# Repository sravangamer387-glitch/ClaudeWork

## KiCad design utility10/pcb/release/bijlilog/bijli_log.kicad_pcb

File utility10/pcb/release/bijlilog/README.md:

# Bijli Log (power-cut logger) - main board (rev B)

Power-cut logger: USB-C 5 V, 3.3 V LDO, 2 x AAA backup (Schottky OR), OLED, RTC module, mains-present sense.

**Status: engineering release, software-verified only (ERC on the netlist, KiCad DRC, netlist cross-check, SPICE where noted). Not yet built, not reviewed by a second engineer, not certified.**

## Specification
- Board 68 x 52 mm, 2 layers, 1.6 mm FR-4, 1 oz copper, rounded corners R2.5 mm, 4 x M2.5 mounting holes, 2 fiducials.
- Rules used: min track 0.2 mm (power 0.4 mm), min clearance 0.2 mm, via 0.6/0.3 mm, GND pour on both layers, 78 stitching vias.
- Finish: ENIG recommended (HASL lead-free acceptable); green mask, white silk; IPC class 2.
- 31 parts, 19 nets.

## Circuit description
- VBUS -> PTC -> +5V -> AP2112K-3.3 -> +3V3 -> Schottky -> VSYS; battery -> Schottky -> VSYS. Drop about 0.3 V; at 4 MHz the MCU runs down to 1.8 V.
- MAINS = VBUS divided by 100 k/100 k: high while the adapter is powered, low in a cut; the firmware stamps the start (RTC) and measures the duration (pc_* engine).

## Power
Run about 3 mA incl. OLED off most of the time; on battery only during cuts.

## Verification
| Check | Result |
|---|---|
| Electrical rule check on the netlist (own ERC: unconnected pins, single-pin nets, output conflicts, unpowered supplies, symbol/footprint pin match) | 0 errors, 0 warnings |
| KiCad DRC | 0 errors, 0 warnings; unconnected pads: 0 |
| Schematic netlist equals PCB netlist | yes |
| Router failures | 0 |
| 3D STEP export | yes |
| Independent Gerber parse (gerbonara): layers parsed, outline size equals the design | 9 layers, outline [68.1, 52.1] mm, match |

Enclosure (prototype shell for 3D printing): outer 83.2 x 67.2 x 34.8 mm, collision/opening check: pass

## Bill of materials
| Ref | Value | Footprint | Manufacturer part | LCSC # | LCSC status |
|---|---|---|---|---|---|
| U1 | ATmega328P-AU | TQFP-32_7x7mm_P0.8mm | ATMEGA328P-AU | C14877 | verified |
| C1 | 100n | C_0603_1608Metric | Samsung CL10B104KB8NNNC 0603 100nF X7R 50V | C1591 | verified |
| C2 | 100n | C_0603_1608Metric | Samsung CL10B104KB8NNNC 0603 100nF X7R 50V | C1591 | verified |
| C3 | 100n | C_0603_1608Metric | Samsung CL10B104KB8NNNC 0603 100nF X7R 50V | C1591 | verified |
| R7 | 10k | R_0603_1608Metric | 0603 10k 1% | C25804 | verified |
| J2 | ISP | PinHeader_2x03_P2.54mm_Vertical | HCTL PZ254-2-03-Z-8.5 (ZHOURI C5116479 had only 340 in stock) | C2894964 | verified |
| J1 | USB-C 5V | USB_C_Receptacle_HRO_TYPE-C-31-M-12 | TYPE-C-31-M-12 | C165948 | verified |
| F1 | PTC 500mA | Fuse_1206_3216Metric | Littelfuse 1206L050YR (6 V) | C163512 | verified |
| D3 | SMAJ5.0A | D_SMA | Littelfuse SMAJ5.0A | C83329 | verified |
| R1 | 5.1k | R_0603_1608Metric | 0603 5.1k 1% | C23186 | verified |
| R2 | 5.1k | R_0603_1608Metric | 0603 5.1k 1% | C23186 | verified |
| C5 | 10u | C_0805_2012Metric | 0805 10uF X5R | C15850 | verified |
| D1 | Green | LED_0603_1608Metric | Hubei KENTO KT-0603YG yellow-green 570 nm, Vf about 2 V (lights well from 3.3 V with 1 k; the Everlight 19-217 green was out of stock) | C2289 | verified |
| R5 | 1k | R_0603_1608Metric | 0603 1k 1% | C21190 | verified |
| U3 | AP2112K-3.3 | SOT-23-5 | Diodes AP2112K-3.3TRG1 (from the LCSC datasheet link) | C51118 | verified |
| C6 | 1u | C_0603_1608Metric | 0603 1uF X7R | C15849 | verified |
| C7 | 1u | C_0603_1608Metric | 0603 1uF X7R | C15849 | verified |
| D5 | BAT54WS | D_SOD-323 | BORN BAT54WS (300 mA listing) | C5148476 | verified |
| D6 | BAT54WS | D_SOD-323 | BORN BAT54WS (300 mA listing) | C5148476 | verified |
| J6 | BATT 2xAAA backup | JST_PH_B2B-PH-K_1x02_P2.00mm_Vertical | JST B2B-PH-K-S(LF)(SN) | C131337 | verified |
| C8 | 10u | C_0805_2012Metric | 0805 10uF X5R | C15850 | verified |
| R12 | 100k | R_0603_1608Metric | 0603 100k 1% | C25803 | verified |
| R13 | 100k | R_0603_1608Metric | 0603 100k 1% | C25803 | verified |
| J4 | OLED 0.91in I2C | JST_PH_B4B-PH-K_1x04_P2.00mm_Vertical | JST B4B-PH-K-S(LF)(SN) | C131334 | verified |
| J5 | RTC DS3231 module | JST_PH_B4B-PH-K_1x04_P2.00mm_Vertical | JST B4B-PH-K-S(LF)(SN) | C131334 | verified |
| R10 | 4.7k | R_0603_1608Metric | 0603 4.7k 1% | C23162 | verified |
| R11 | 4.7k | R_0603_1608Metric | 0603 4.7k 1% | C23162 | verified |
| SW2 | Scroll / clear | SW_SPST_B3U-1000P | Omron B3U-1000P | C231329 | verified |
| TP1 | TP | TestPoint_Pad_D1.5mm |  |  |  |
| TP2 | TP | TestPoint_Pad_D1.5mm |  |  |  |
| TP3 | TP | TestPoint_Pad_D1.5mm |  |  |  |

`verified` = LCSC number confirmed by web search on 2026-10-31/11-01; `memory` = from my recollection, **check on lcsc.com before ordering**; empty = no number chosen (through-hole connectors, switches, buzzer, test points: hand-assembled or chosen by the buyer). `*_JLC_BOM.csv` / `*_JLC_CPL.csv` list only the parts with an LCSC number; JLCPCB rotation corrections (CPL) must be checked in their viewer.

## Assembly notes
- Reflow (JLCPCB SMT): all SMD parts with an LCSC number. Hand-solder: JST connectors, pin headers, buzzer, switches, test points as listed in the BOM. Fiducials and mounting holes are in the Gerbers.
- Polarity: LED cathode toward GND (silk marks), electrolytic none, diode D2 cathode to +V, Q2 orientation as footprint (SOT-23 pin 1 = gate).
- Programming: ISP header J2 (pin 1 = MISO, square pad). Flash the matching image from `utility10/firmware/release/`: Seeti Counter `4MHz/seeti_prod.hex` (production firmware: timer-triggered 16 kS/s ADC, scan mode to find the real whistle frequency, battery check), Rain Alert `8MHz/rain_alert.hex`, Bijli Meter Reader `8MHz/bijli_meter.hex` (demo-grade firmware, to be hardened).

## Bring-up and test
1. Plug USB: +3V3 = 3.3 V, VSYS about 3.0 V, MAINS (TP3) about 2.5 V.
2. Unplug: MAINS goes low, unit stays alive on the battery, cut logged; replug: duration shown.

## Files
`1_fabrication/` Gerber + drill zip (upload to JLCPCB/any fab), fab notes, copper plot
`2_assembly/` JLC BOM + CPL (SMD parts JLC assembles), full BOM with LCSC numbers for every part, pick-and-place, assembly drawing
`3_design/` KiCad 7 project (pcb, schematic, libs), netlist, STEP model, schematic PDF, renders
`4_enclosure/` printable enclosure (base, screwed lid, battery door, plungers / light pipes / switch extensions) or a mounting plate for a bought IP65 box; dimensions and notes in enclosure.json
`5_verification/` DRC, ERC, verification and readiness reports

## Known limits and review checklist
- Layout was produced by a custom router and software placement; a human layout review (analog routing, ground returns, creepage, connector mechanics, silkscreen) is still required.
- Not verified: EMC, ESD (apart from TVS parts where fitted), thermal, real component tolerances, supplier stock/price, assembly house design-for-manufacture check (run JLCPCB's DFM check on the Gerbers).
- Firmware thresholds are placeholders to be calibrated on prototypes.

## Manufacturing readiness (automatic check)

| Check | Result |
|---|---|
| gerber layers and drill present | PASS |
| drc errors 0 | PASS |
| unconnected 0 | PASS |
| netlist matches schematic | PASS |
| erc errors 0 | PASS |
| independent gerber check clean | PASS |
| every part has lcsc number | PASS |
| every lcsc number verified | PASS |
| cpl rows equal jlc bom parts | PASS |
| step model | PASS |
| KiCad DRC warnings | 0 |
| **Order ready** | **YES** |

Order steps: (1) upload `1_fabrication/*_gerbers.zip`; (2) for assembly upload `2_assembly/*_JLC_BOM.csv` and `*_JLC_CPL.csv`, check the 3D/rotation preview for every polarised part (diodes, ICs, LEDs, electrolytics) because CPL rotations are generated, not hand-checked; (3) buy the through-hole parts listed in `*_BOM_full.csv` marked hand/THT and solder them; (4) re-check stock and the exact LCSC listing for every line before paying.

Limits: the layout is software-generated and has not been reviewed by a PCB engineer; no prototype has been built; the first batch should be treated as a prototype run (order 5 boards).

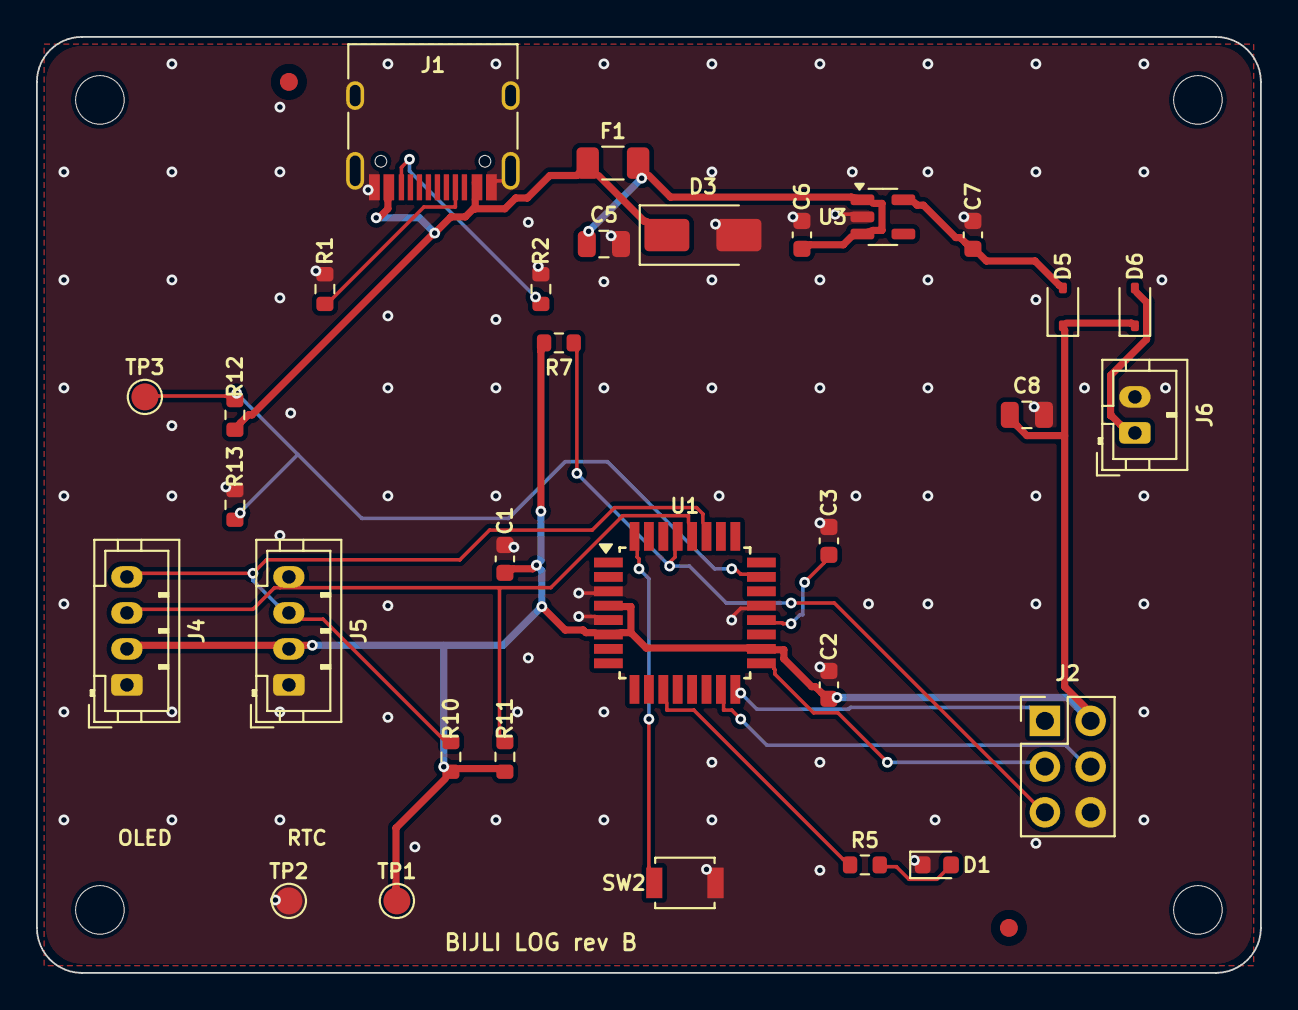
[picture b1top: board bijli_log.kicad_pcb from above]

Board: 2 copper layers, 68.0 x 52.0 mm, 37 parts (0 on the bottom side), 19 nets.

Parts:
C1, C2, C3: 100n; C_0603_1608Metric
C5, C8: 10u; C_0805_2012Metric
C6, C7: 1u; C_0603_1608Metric
D1: Green; LED_0603_1608Metric
D3: SMAJ5.0A; D_SMA
D5, D6: BAT54WS; D_SOD-323
F1: PTC 500mA; Fuse_1206_3216Metric
FID1, FID2: Fiducial; Fiducial_1mm_Mask2mm
H1, H2, H3, H4: M2.5; MountingHole_2.7mm_M2.5
J1: USB-C 5V; USB_C_Receptacle_HRO_TYPE-C-31-M-12
J2: ISP; PinHeader_2x03_P2.54mm_Vertical
J4: OLED 0.91in I2C; JST_PH_B4B-PH-K_1x04_P2.00mm_Vertical
J5: RTC DS3231 module; JST_PH_B4B-PH-K_1x04_P2.00mm_Vertical
J6: BATT 2xAAA backup; JST_PH_B2B-PH-K_1x02_P2.00mm_Vertical
R1, R2: 5.1k; R_0603_1608Metric
R5: 1k; R_0603_1608Metric
R7: 10k; R_0603_1608Metric
R10, R11: 4.7k; R_0603_1608Metric
R12, R13: 100k; R_0603_1608Metric
SW2: Scroll / clear; SW_SPST_B3U-1000P
TP1, TP2, TP3: TP; TestPoint_Pad_D1.5mm
U1: ATmega328P-AU; TQFP-32_7x7mm_P0.8mm
U3: AP2112K-3.3; SOT-23-5

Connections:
+3V3: C7.1, D5.2, U3.5
+5V: C5.1, C6.1, F1.2, U3.1, U3.3
AREF: C3.1, U1.20
BAT_P: D6.2, J6.1
BTN: SW2.1, U1.32
CC1: J1.A5, R1.1
CC2: J1.B5, R2.1
D1_A: D1.2, R5.2
GND: C1.2, C2.2, C3.2, C5.2, C6.2, C7.2, C8.2, D1.1, D3.2, J1.A1, J1.A12, J1.B1, J1.B12, J1.S1, J2.6, J4.1, J5.1, J6.2, R1.2, R2.2, R13.2, SW2.2, TP2.1, U1.3, U1.5, U1.21, U3.2
LED: R5.1, U1.11
MAINS: R12.2, R13.1, TP3.1, U1.23
MISO: J2.1, U1.16
MOSI: J2.4, U1.15
RESET: J2.5, R7.2, U1.29
SCK: J2.3, U1.17
SCL: J4.3, J5.4, R11.2, U1.28
SDA: J4.4, J5.3, R10.2, U1.27
VBUS: D3.1, F1.1, J1.A4, J1.A9, J1.B4, J1.B9, R12.1
VSYS: C1.1, C2.1, C8.1, D5.1, D6.1, J2.2, J4.2, J5.2, R7.1, R10.1, R11.1, TP1.1, U1.4, U1.6, U1.18

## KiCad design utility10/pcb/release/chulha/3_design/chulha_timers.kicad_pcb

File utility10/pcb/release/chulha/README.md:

# Chulha Timers - main board (rev B)

Four independent kitchen timers: four channel buttons, TM1637 6-digit display module, loud buzzer, 3 x AAA.

**Status: engineering release, software-verified only (ERC on the netlist, KiCad DRC, netlist cross-check, SPICE where noted). Not yet built, not reviewed by a second engineer, not certified.**

## Specification
- Board 72 x 48 mm, 2 layers, 1.6 mm FR-4, 1 oz copper, rounded corners R2.5 mm, 4 x M2.5 mounting holes, 2 fiducials.
- Rules used: min track 0.2 mm (power 0.4 mm), min clearance 0.2 mm, via 0.6/0.3 mm, GND pour on both layers, 86 stitching vias.
- Finish: ENIG recommended (HASL lead-free acceptable); green mask, white silk; IPC class 2.
- 22 parts, 18 nets.

## Circuit description
- Channel buttons CH1-CH4 on PD2-PD5 (internal pull-ups); TM1637 on PC4/PC5 (DIO/CLK) through the J4 module header; buzzer driver as on the other boards.
- Tap adds one minute, hold 1 s clears; each channel rings separately (firmware engine ct_*, tested).

## Power
Display on: about 10 mA + MCU 3 mA; sleep between button presses and blank the display after 20 s idle -> months on 3 x AAA.

## Verification
| Check | Result |
|---|---|
| Electrical rule check on the netlist (own ERC: unconnected pins, single-pin nets, output conflicts, unpowered supplies, symbol/footprint pin match) | 0 errors, 0 warnings |
| KiCad DRC | 0 errors, 0 warnings; unconnected pads: 0 |
| Schematic netlist equals PCB netlist | yes |
| Router failures | 0 |
| 3D STEP export | yes |
| Independent Gerber parse (gerbonara): layers parsed, outline size equals the design | 9 layers, outline [72.1, 48.1] mm, match |

Enclosure (prototype shell for 3D printing): outer 87.2 x 63.5 x 35.8 mm, collision/opening check: pass

## Bill of materials
| Ref | Value | Footprint | Manufacturer part | LCSC # | LCSC status |
|---|---|---|---|---|---|
| U1 | ATmega328P-AU | TQFP-32_7x7mm_P0.8mm | ATMEGA328P-AU | C14877 | verified |
| C1 | 100n | C_0603_1608Metric | Samsung CL10B104KB8NNNC 0603 100nF X7R 50V | C1591 | verified |
| C2 | 100n | C_0603_1608Metric | Samsung CL10B104KB8NNNC 0603 100nF X7R 50V | C1591 | verified |
| C3 | 100n | C_0603_1608Metric | Samsung CL10B104KB8NNNC 0603 100nF X7R 50V | C1591 | verified |
| R7 | 10k | R_0603_1608Metric | 0603 10k 1% | C25804 | verified |
| J2 | ISP | PinHeader_2x03_P2.54mm_Vertical | HCTL PZ254-2-03-Z-8.5 (ZHOURI C5116479 had only 340 in stock) | C2894964 | verified |
| J1 | BATT 3xAAA | JST_PH_B2B-PH-K_1x02_P2.00mm_Vertical | JST B2B-PH-K-S(LF)(SN) | C131337 | verified |
| SW1 | Power | SW_SPDT_PCM12 | C&K PCM12SMTR | C221841 | verified |
| Q2 | AO3401A | SOT-23 | AO3401A | C15127 | verified |
| C4 | 10u | C_0805_2012Metric | 0805 10uF X5R | C15850 | verified |
| BZ1 | Buzzer | Buzzer_12x9.5RM7.6 | YUEXIN KC1206 16 ohm passive magnetic 12x9.5 mm (2048 Hz) | C781869 | verified |
| Q1 | MMBT3904 | SOT-23 | MMBT3904 | C20526 | verified |
| D2 | 1N4148WS | D_SOD-323 | 1N4148WS | C2128 | verified |
| R6 | 1k | R_0603_1608Metric | 0603 1k 1% | C21190 | verified |
| SW2 | CH1 | SW_SPST_B3U-1000P | Omron B3U-1000P | C231329 | verified |
| SW3 | CH2 | SW_SPST_B3U-1000P | Omron B3U-1000P | C231329 | verified |
| SW4 | CH3 | SW_SPST_B3U-1000P | Omron B3U-1000P | C231329 | verified |
| SW5 | CH4 | SW_SPST_B3U-1000P | Omron B3U-1000P | C231329 | verified |
| J4 | TM1637 display | JST_PH_B4B-PH-K_1x04_P2.00mm_Vertical | JST B4B-PH-K-S(LF)(SN) | C131334 | verified |
| TP1 | TP | TestPoint_Pad_D1.5mm |  |  |  |
| TP2 | TP | TestPoint_Pad_D1.5mm |  |  |  |
| TP3 | TP | TestPoint_Pad_D1.5mm |  |  |  |

`verified` = LCSC number confirmed by web search on 2026-10-31/11-01; `memory` = from my recollection, **check on lcsc.com before ordering**; empty = no number chosen (through-hole connectors, switches, buzzer, test points: hand-assembled or chosen by the buyer). `*_JLC_BOM.csv` / `*_JLC_CPL.csv` list only the parts with an LCSC number; JLCPCB rotation corrections (CPL) must be checked in their viewer.

## Assembly notes
- Reflow (JLCPCB SMT): all SMD parts with an LCSC number. Hand-solder: JST connectors, pin headers, buzzer, switches, test points as listed in the BOM. Fiducials and mounting holes are in the Gerbers.
- Polarity: LED cathode toward GND (silk marks), electrolytic none, diode D2 cathode to +V, Q2 orientation as footprint (SOT-23 pin 1 = gate).
- Programming: ISP header J2 (pin 1 = MISO, square pad). Flash the matching image from `utility10/firmware/release/`: Seeti Counter `4MHz/seeti_prod.hex` (production firmware: timer-triggered 16 kS/s ADC, scan mode to find the real whistle frequency, battery check), Rain Alert `8MHz/rain_alert.hex`, Bijli Meter Reader `8MHz/bijli_meter.hex` (demo-grade firmware, to be hardened).

## Bring-up and test
1. Power on: display shows 0; tap CH1: +1 min counts down.
2. Ring: each channel's buzzer pattern stops with its own button.

## Files
`1_fabrication/` Gerber + drill zip (upload to JLCPCB/any fab), fab notes, copper plot
`2_assembly/` JLC BOM + CPL (SMD parts JLC assembles), full BOM with LCSC numbers for every part, pick-and-place, assembly drawing
`3_design/` KiCad 7 project (pcb, schematic, libs), netlist, STEP model, schematic PDF, renders
`4_enclosure/` printable enclosure (base, screwed lid, battery door, plungers / light pipes / switch extensions) or a mounting plate for a bought IP65 box; dimensions and notes in enclosure.json
`5_verification/` DRC, ERC, verification and readiness reports

## Known limits and review checklist
- Layout was produced by a custom router and software placement; a human layout review (analog routing, ground returns, creepage, connector mechanics, silkscreen) is still required.
- Not verified: EMC, ESD (apart from TVS parts where fitted), thermal, real component tolerances, supplier stock/price, assembly house design-for-manufacture check (run JLCPCB's DFM check on the Gerbers).
- Firmware thresholds are placeholders to be calibrated on prototypes.

## Manufacturing readiness (automatic check)

| Check | Result |
|---|---|
| gerber layers and drill present | PASS |
| drc errors 0 | PASS |
| unconnected 0 | PASS |
| netlist matches schematic | PASS |
| erc errors 0 | PASS |
| independent gerber check clean | PASS |
| every part has lcsc number | PASS |
| every lcsc number verified | PASS |
| cpl rows equal jlc bom parts | PASS |
| step model | PASS |
| KiCad DRC warnings | 0 |
| **Order ready** | **YES** |

Order steps: (1) upload `1_fabrication/*_gerbers.zip`; (2) for assembly upload `2_assembly/*_JLC_BOM.csv` and `*_JLC_CPL.csv`, check the 3D/rotation preview for every polarised part (diodes, ICs, LEDs, electrolytics) because CPL rotations are generated, not hand-checked; (3) buy the through-hole parts listed in `*_BOM_full.csv` marked hand/THT and solder them; (4) re-check stock and the exact LCSC listing for every line before paying.

Limits: the layout is software-generated and has not been reviewed by a PCB engineer; no prototype has been built; the first batch should be treated as a prototype run (order 5 boards).

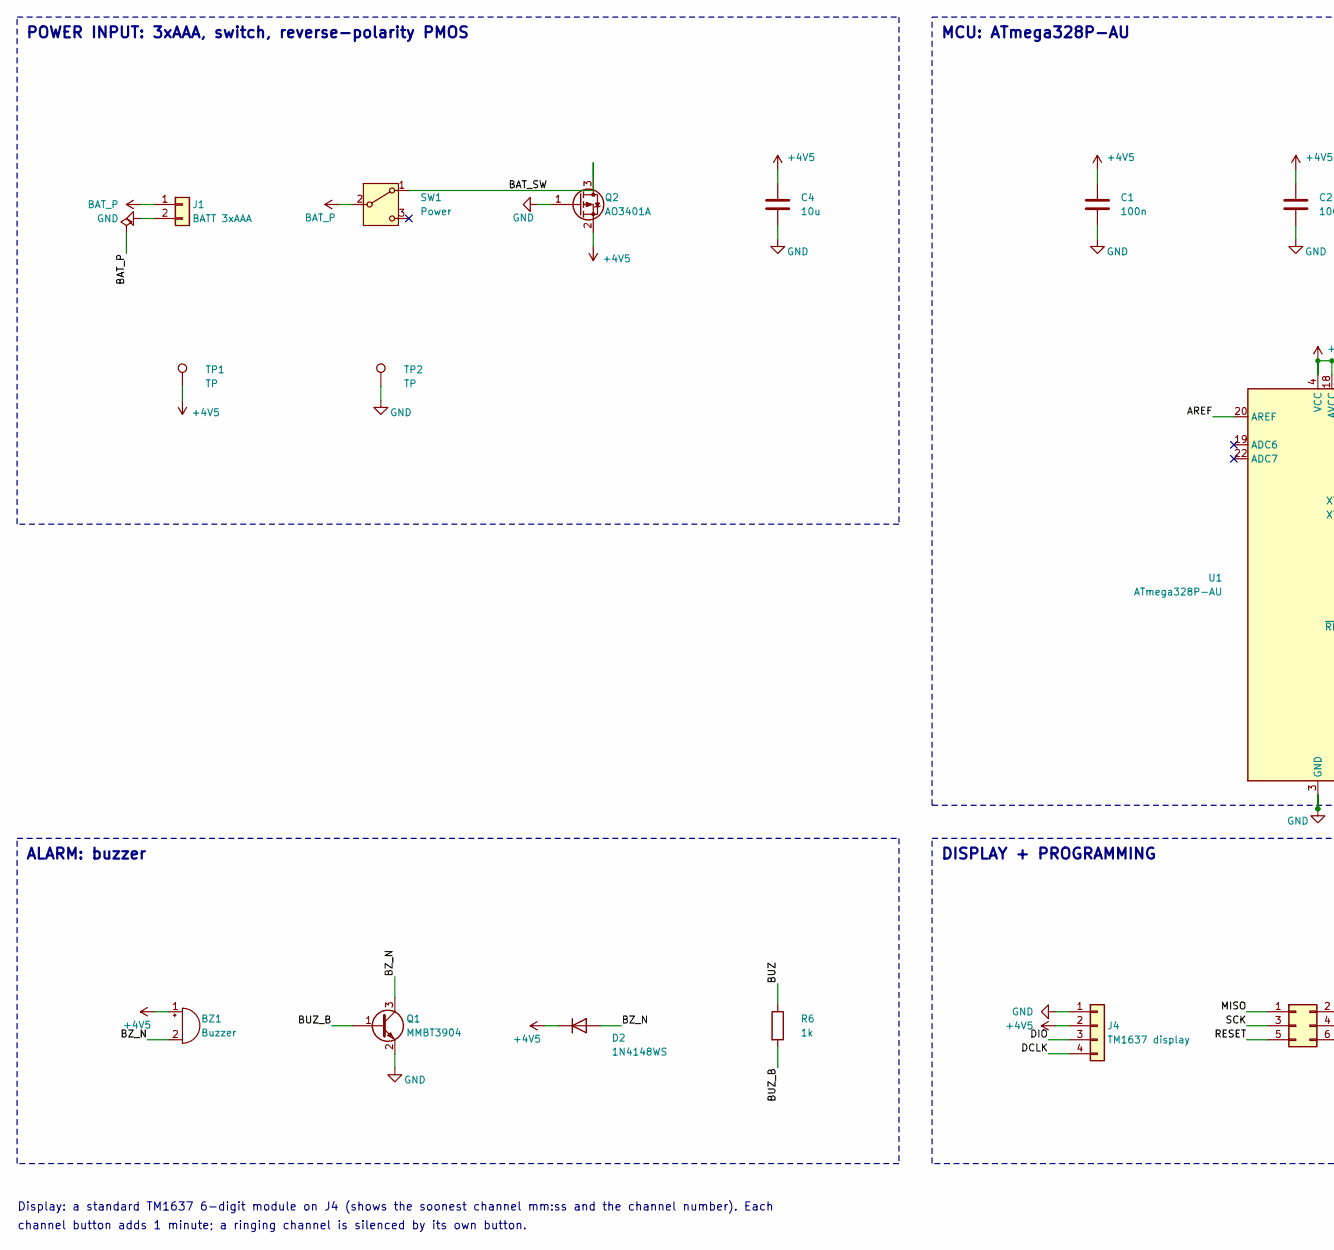
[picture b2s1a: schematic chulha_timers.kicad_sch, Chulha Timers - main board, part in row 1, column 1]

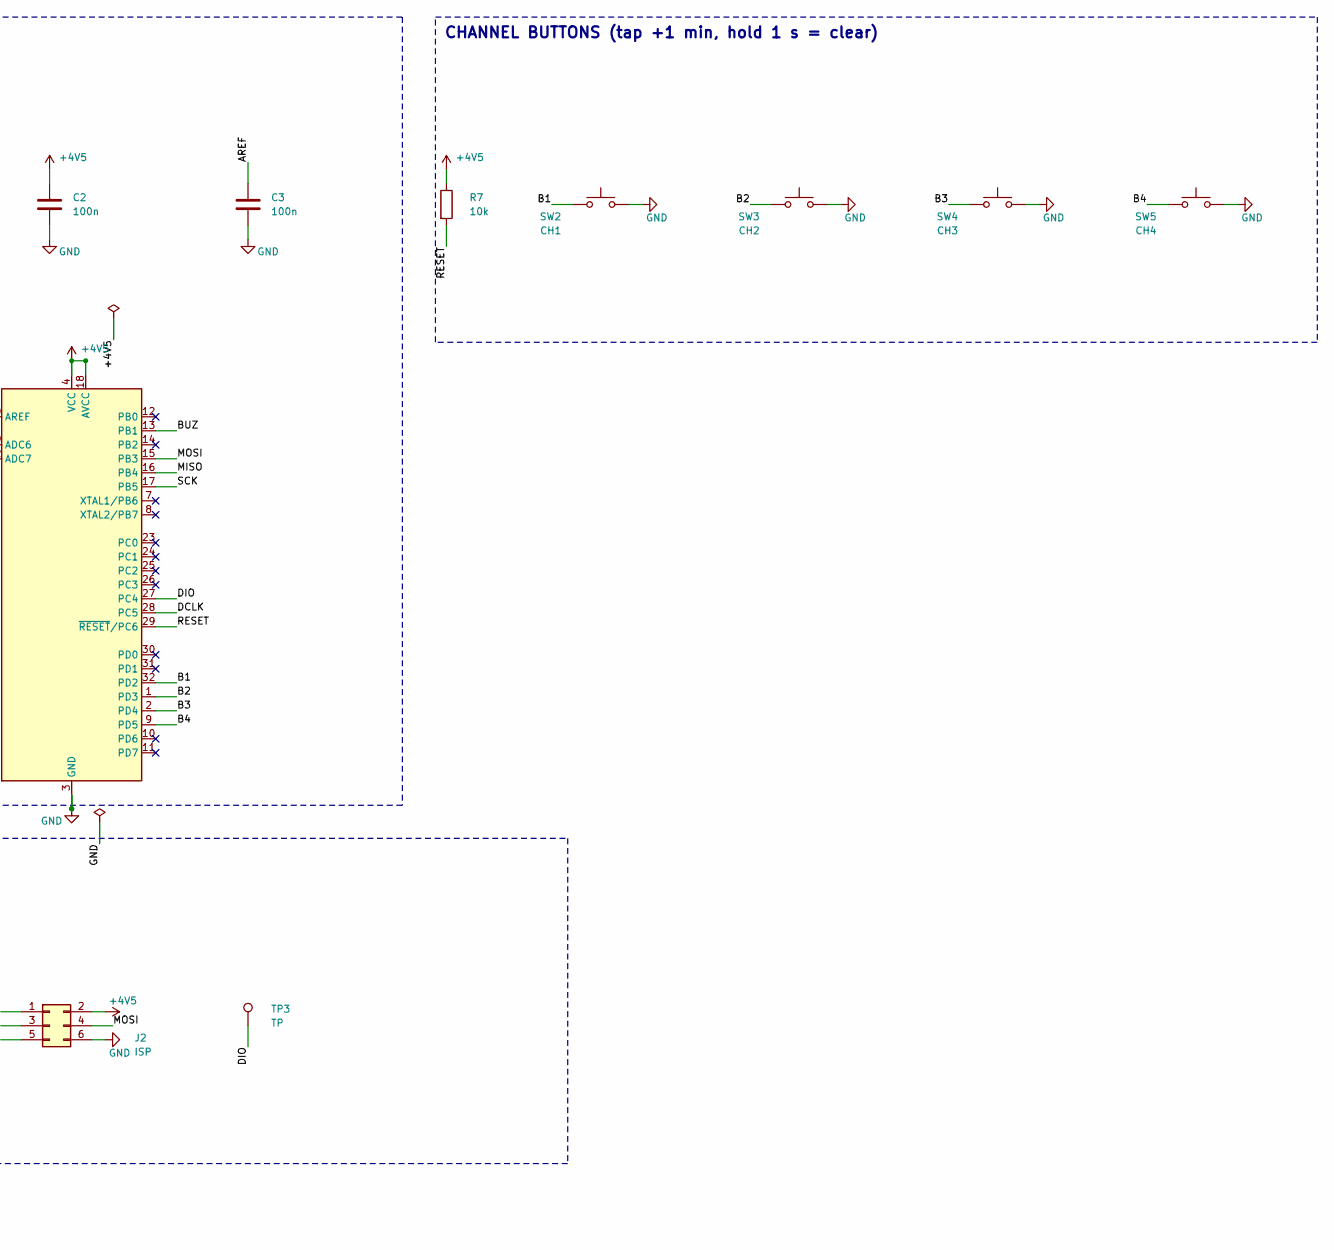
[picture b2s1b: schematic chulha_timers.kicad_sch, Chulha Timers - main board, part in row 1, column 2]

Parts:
BZ1: Buzzer; Buzzer_12x9.5RM7.6
C1, C2, C3: 100n; C_0603_1608Metric
C4: 10u; C_0805_2012Metric
D2: 1N4148WS; D_SOD-323
J1: BATT 3xAAA; JST_PH_B2B-PH-K_1x02_P2.00mm_Vertical
J2: ISP; PinHeader_2x03_P2.54mm_Vertical
J4: TM1637 display; JST_PH_B4B-PH-K_1x04_P2.00mm_Vertical
Q1: MMBT3904; SOT-23
Q2: AO3401A; SOT-23
R6: 1k; R_0603_1608Metric
R7: 10k; R_0603_1608Metric
SW1: Power; SW_SPDT_PCM12
SW2: CH1; SW_SPST_B3U-1000P
SW3: CH2; SW_SPST_B3U-1000P
SW4: CH3; SW_SPST_B3U-1000P
SW5: CH4; SW_SPST_B3U-1000P
TP1, TP2, TP3: TP; TestPoint_Pad_D1.5mm
U1: ATmega328P-AU; TQFP-32_7x7mm_P0.8mm

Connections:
+4V5: BZ1.1 (+), C1.1, C2.1, C4.1, D2.1 (K), J2.2, J4.2, Q2.2 (S), R7.1, TP1.1, U1.4 (VCC), U1.6 (VCC), U1.18 (AVCC)
AREF: C3.1, U1.20 (AREF)
B1: SW2.1, U1.32 (PD2)
B2: SW3.1, U1.1 (PD3)
B3: SW4.1, U1.2 (PD4)
B4: SW5.1, U1.9 (PD5)
BAT_P: J1.1, SW1.2 (B)
BAT_SW: Q2.3 (D), SW1.1 (A)
BUZ: R6.1, U1.13 (PB1)
BUZ_B: Q1.1 (B), R6.2
BZ_N: BZ1.2 (-), D2.2 (A), Q1.3 (C)
DCLK: J4.4, U1.28 (PC5)
DIO: J4.3, TP3.1, U1.27 (PC4)
GND: C1.2, C2.2, C3.2, C4.2, J1.2, J2.6, J4.1, Q1.2 (E), Q2.1 (G), SW2.2, SW3.2, SW4.2, SW5.2, TP2.1, U1.3 (GND), U1.5 (GND), U1.21 (GND)
MISO: J2.1, U1.16 (PB4)
MOSI: J2.4, U1.15 (PB3)
RESET: J2.5, R7.2, U1.29 (~RESET/PC6)
SCK: J2.3, U1.17 (PB5)

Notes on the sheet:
POWER INPUT: 3xAAA, switch, reverse-polarity PMOS
MCU: ATmega328P-AU
CHANNEL BUTTONS (tap +1 min, hold 1 s = clear)
ALARM: buzzer
DISPLAY + PROGRAMMING
Display: a standard TM1637 6-digit module on J4 (shows the soonest channel mm:ss and the channel number). Each
channel button adds 1 minute; a ringing channel is silenced by its own button.

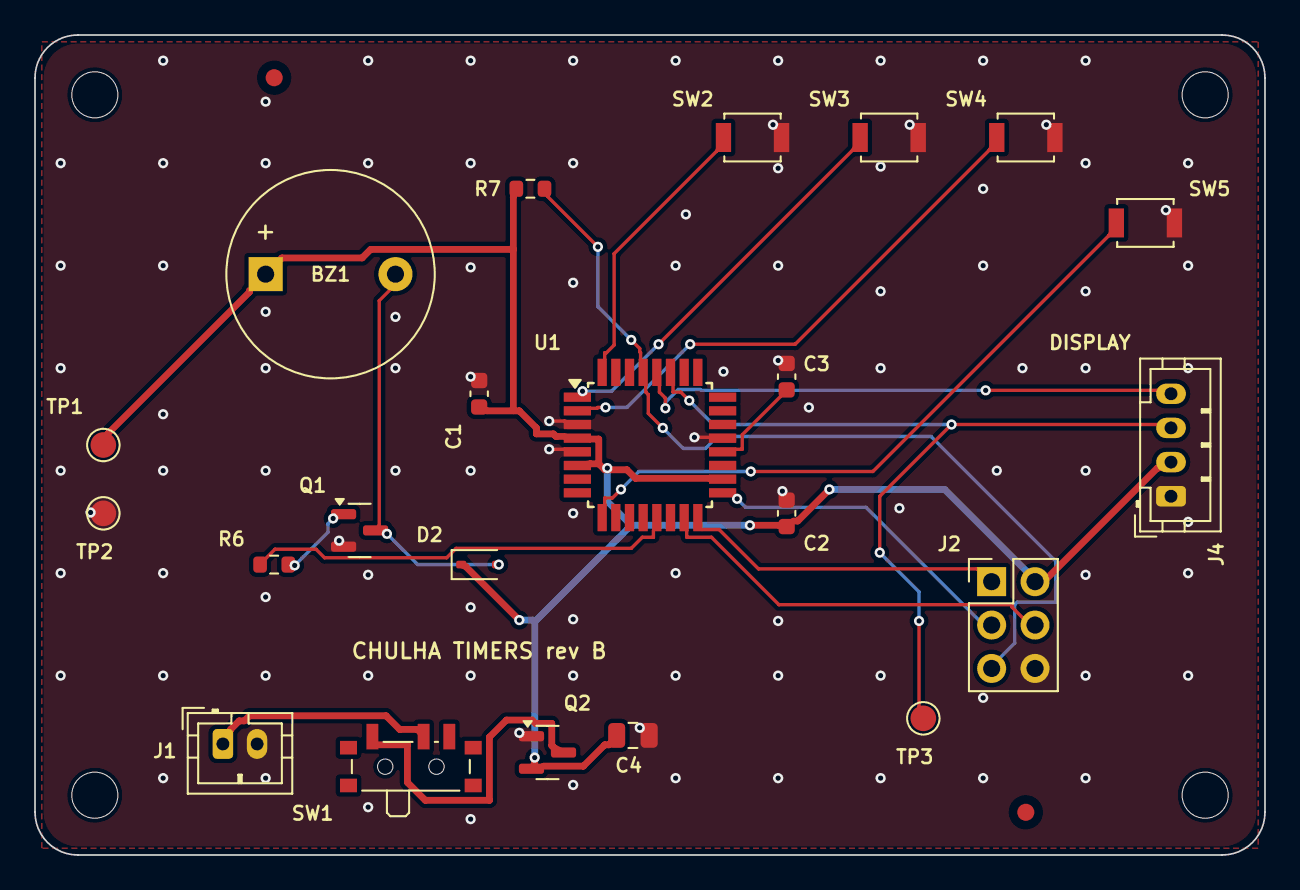
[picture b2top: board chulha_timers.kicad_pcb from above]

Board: 2 copper layers, 72.0 x 48.0 mm, 28 parts (0 on the bottom side), 18 nets.

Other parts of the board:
FID1, FID2: Fiducial; Fiducial_1mm_Mask2mm
H1, H2, H3, H4: M2.5; MountingHole_2.7mm_M2.5
